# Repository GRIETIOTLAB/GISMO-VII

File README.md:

# GISMO-VII
This version of GISMO is designed with Grove connectors   
The board has :  
2 Analog Grove ports  
2 Digital Grove ports  
2 I2C Grove ports  
1 UART Grove port  
1 Grove port with 5V supply

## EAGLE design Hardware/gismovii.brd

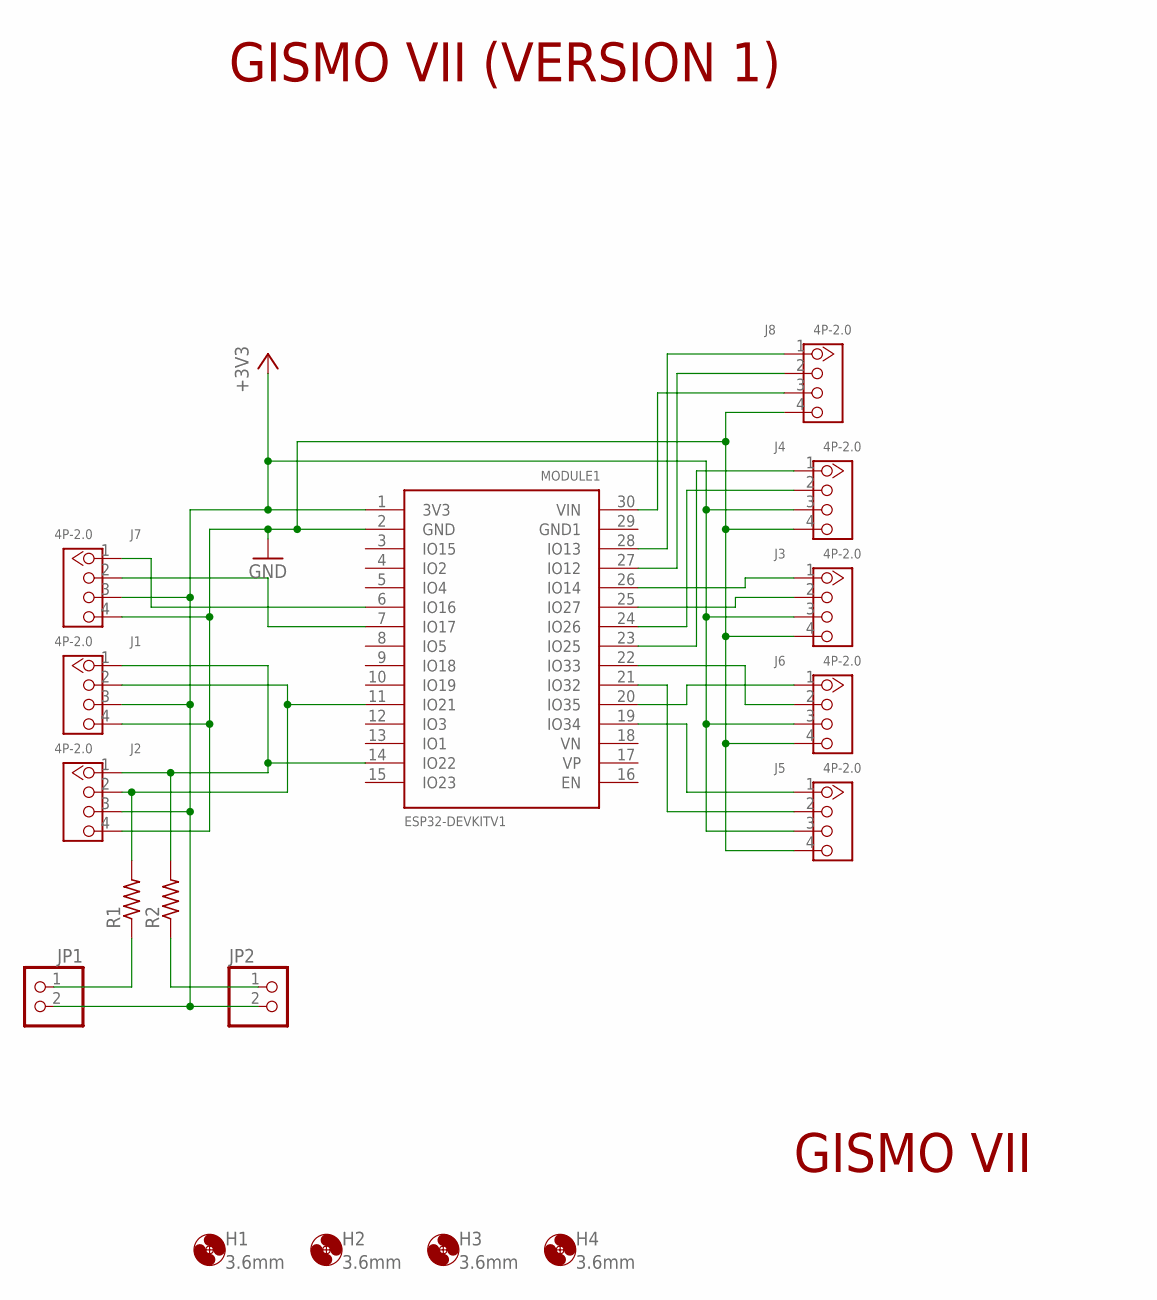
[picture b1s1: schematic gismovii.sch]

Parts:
H1, H2, H3, H4: 3.6mm; 3,6
J1, J2, J3, J4, J5, J6, J7, J8: 4P-2.0; HW4-2.0
JP1, JP2: PINHD-1X2; 1X02
MODULE1: ESP32DEVKITV1; ESP32-DEVKITV1
R1, R2: R-US_0204/7; 0204/7

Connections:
+3V3: J1.3, J2.3, J3.3, J4.3, J5.3, J6.3, J7.3, JP1.2, JP2.2, MODULE1.1 (3V3)
GND: J1.4, J2.4, J3.4, J4.4, J5.4, J6.4, J7.4, J8.4, MODULE1.2 (GND)
unnamed: J1.2, J2.2, MODULE1.11 (IO21), R1.2
unnamed: J1.1, J2.1, MODULE1.14 (IO22), R2.2
unnamed: J7.2, MODULE1.7 (IO17)
unnamed: J7.1, MODULE1.6 (IO16)
unnamed: J5.1, MODULE1.19 (IO34)
unnamed: J4.2, MODULE1.24 (IO26)
unnamed: J4.1, MODULE1.23 (IO25)
unnamed: J3.1, MODULE1.26 (IO14)
unnamed: J3.2, MODULE1.25 (IO27)
unnamed: J6.1, MODULE1.20 (IO35)
unnamed: J6.2, MODULE1.22 (IO33)
unnamed: JP2.1, R2.1
unnamed: JP1.1, R1.1
unnamed: J5.2, MODULE1.21 (IO32)
unnamed: J8.3, MODULE1.30 (VIN)
unnamed: J8.2, MODULE1.27 (IO12)
unnamed: J8.1, MODULE1.28 (IO13)

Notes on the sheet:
GISMO VII (VERSION 1)
GISMO VII

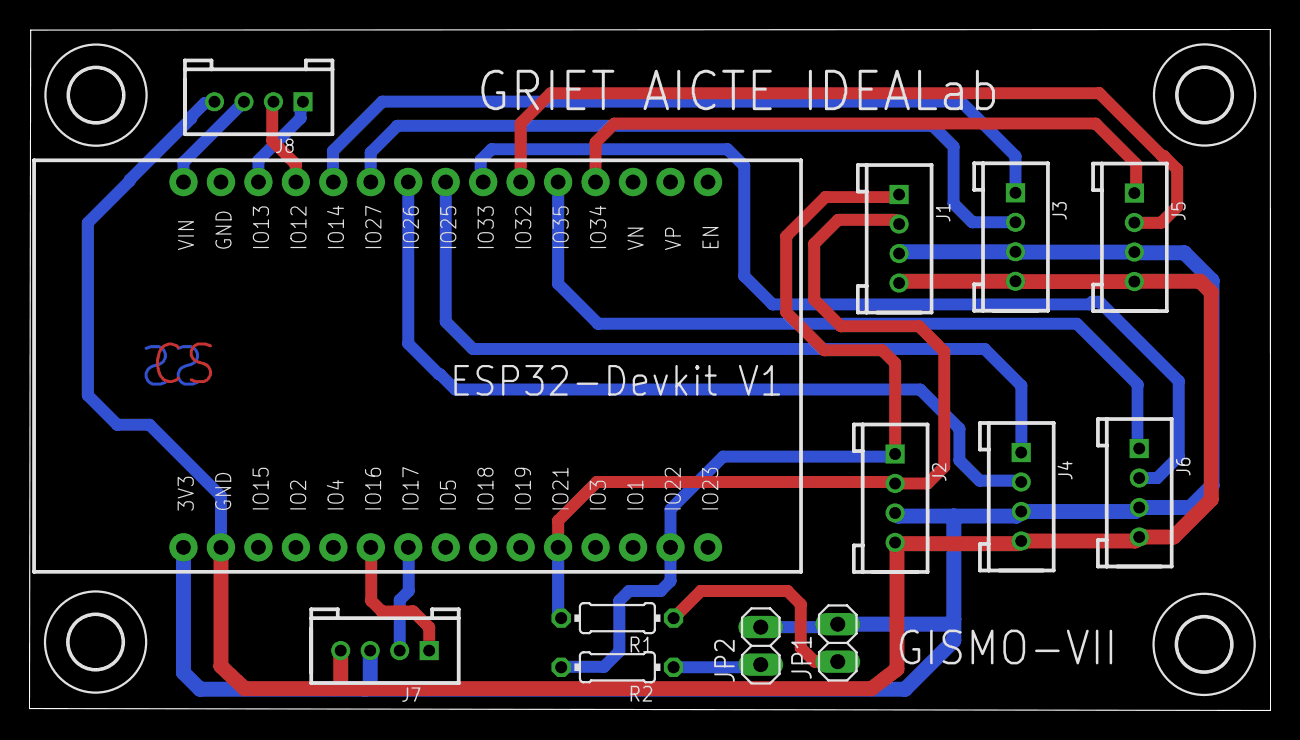
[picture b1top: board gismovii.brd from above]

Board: 2 copper layers, 84.1 x 46.2 mm, 17 parts (0 on the bottom side), 19 nets.
